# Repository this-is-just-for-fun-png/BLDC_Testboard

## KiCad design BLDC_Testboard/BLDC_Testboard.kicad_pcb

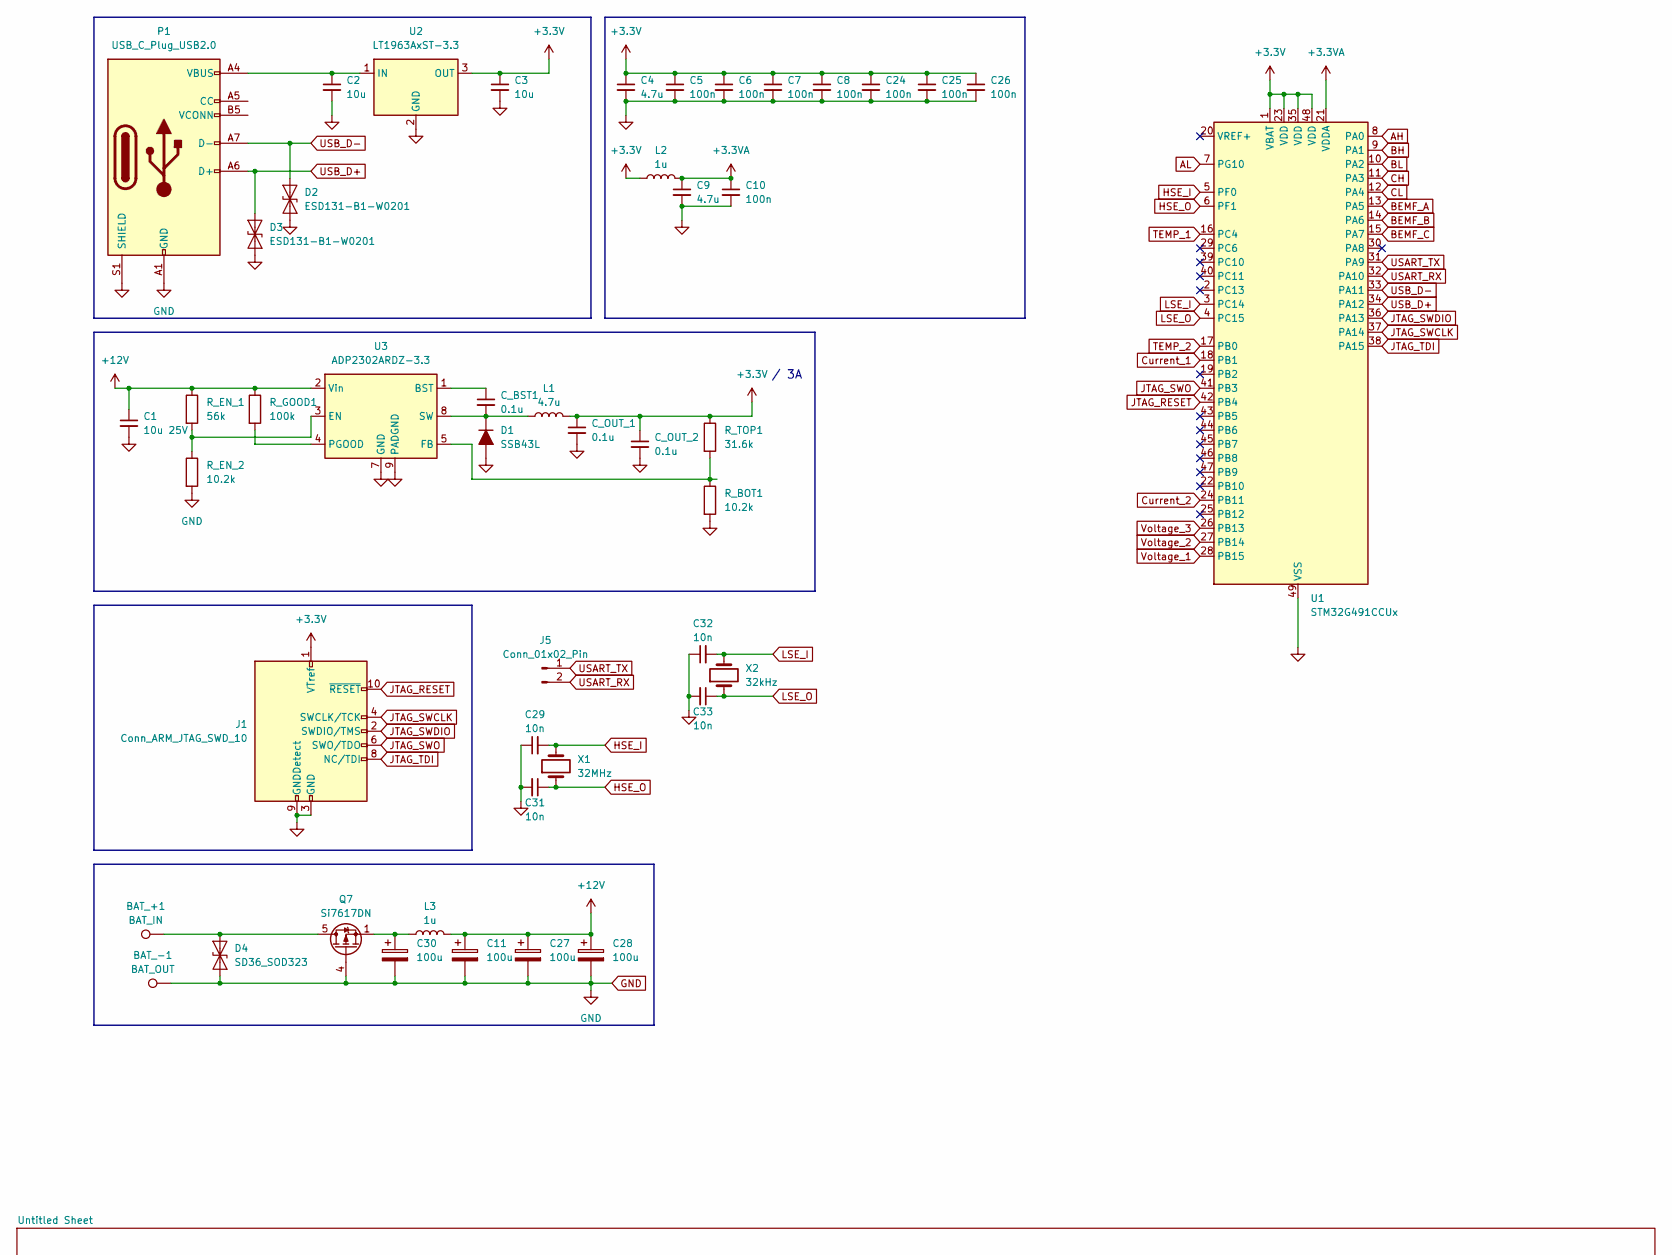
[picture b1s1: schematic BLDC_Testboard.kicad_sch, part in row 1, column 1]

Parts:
BAT_+1: BAT_IN; SolderWire-2.5sqmm_1x01_D2.4mm_OD4.4mm
BAT_-1: BAT_OUT; SolderWire-2.5sqmm_1x01_D2.4mm_OD4.4mm
C1: 10u 25V; C_0201_0603Metric
C2, C3: 10u; C_0201_0603Metric
C4, C9: 4.7u; C_0201_0603Metric
C5, C6, C7, C8, C10, C24, C25, C26: 100n; C_0201_0603Metric
C11, C27, C28, C30: 100u; CP_Elec_3x5.3
C29, C31, C32, C33: 10n; C_0201_0603Metric
C_BST1: 0.1u; C_0201_0603Metric
C_OUT_1, C_OUT_2: 0.1u; C_0201_0603Metric
D1: SSB43L; D_SMB
D2, D3: ESD131-B1-W0201; Infineon_SG-WLL-2-3_0.58x0.28_P0.36mm
D4: SD36_SOD323; D_SOD-323
J1: Conn_ARM_JTAG_SWD_10; PinHeader_2x05_P1.27mm_Vertical_SMD
J5: Conn_01x02_Pin; PinHeader_1x02_P1.00mm_Vertical
L1: 4.7u; L_0201_0603Metric
L2, L3: 1u; L_0201_0603Metric
P1: USB_C_Plug_USB2.0; USB_C_Receptacle_Amphenol_12401610E4-2A
Q7: Si7617DN; Vishay_PowerPAK_1212-8_Single
R_BOT1: 10.2k; R_0201_0603Metric_Pad0.64x0.40mm_HandSolder
R_EN_1: 56k; R_0201_0603Metric_Pad0.64x0.40mm_HandSolder
R_EN_2: 10.2k; R_0201_0603Metric_Pad0.64x0.40mm_HandSolder
R_GOOD1: 100k; R_0201_0603Metric_Pad0.64x0.40mm_HandSolder
R_TOP1: 31.6k; R_0603_1608Metric_Pad0.98x0.95mm_HandSolder
U1: STM32G491CCUx; QFN-48-1EP_7x7mm_P0.5mm_EP5.6x5.6mm
U2: LT1963AxST-3.3; SOT-223-3_TabPin2
U3: ADP2302ARDZ-3.3; SOIC-8-1EP_3.9x4.9mm_P1.27mm_EP2.29x3mm
X1: 32MHz; Crystal_SMD_2012-2Pin_2.0x1.2mm_HandSoldering
X2: 32kHz; Crystal_SMD_2012-2Pin_2.0x1.2mm_HandSoldering

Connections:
+3.3V: C3.1, C4.1, C5.1, C6.1, C7.1, C8.1, C24.1, C25.1, C26.1, C_OUT_1.1, C_OUT_2.1, J1.1 (VTref), L1.2, L2.1, R_TOP1.1, U1.1 (VBAT), U1.23 (VDD), U1.35 (VDD), U1.48 (VDD), U2.3 (OUT); also elsewhere on the board
+3.3VA: C9.1, C10.1, L2.2, U1.21 (VDDA)
+12V: C1.1, C11.1, C27.1, C28.1, L3.2, R_EN_1.1, R_GOOD1.1, U3.2 (Vin); also elsewhere on the board
AH: U1.8 (PA0); also elsewhere on the board
AL: U1.7 (PG10); also elsewhere on the board
BEMF_A: U1.13 (PA5); also elsewhere on the board
BEMF_B: U1.14 (PA6); also elsewhere on the board
BEMF_C: U1.15 (PA7); also elsewhere on the board
BH: U1.9 (PA1); also elsewhere on the board
BL: U1.10 (PA2); also elsewhere on the board
CH: U1.11 (PA3); also elsewhere on the board
CL: U1.12 (PA4); also elsewhere on the board
Current_1: U1.18 (PB1)
Current_2: U1.24 (PB11)
Current_SP1-: BAT_-1.1, C1.2, C2.2, C3.2, C4.2, C5.2, C6.2, C7.2, C8.2, C9.2, C10.2, C11.2, C24.2, C25.2, C26.2, C27.2, C28.2, C29.1, C30.2, C31.2, C32.1, C33.2, C_OUT_1.2, C_OUT_2.2, D1.2 (A), D2.1 (A1), D3.1 (A1), D4.1 (A1), J1.3 (GND), J1.5 (GND), J1.9 (GNDDetect), P1.A1 (GND), P1.A12 (GND), P1.B1 (GND), P1.B12 (GND), P1.S1 (SHIELD), Q7.4 (G), R_BOT1.2, R_EN_2.2, U1.49 (VSS), U2.2 (GND), U3.7 (GND), U3.9 (PADGND); also elsewhere on the board
HSE_I: C29.2, U1.5 (PF0), X1.2
HSE_O: C31.1, U1.6 (PF1), X1.1
JTAG_RESET: J1.10 (~RESET), U1.42 (PB4)
JTAG_SWCLK: J1.4 (SWCLK/TCK), U1.37 (PA14)
JTAG_SWDIO: J1.2 (SWDIO/TMS), U1.36 (PA13)
JTAG_SWO: J1.6 (SWO/TDO), U1.41 (PB3)
JTAG_TDI: J1.8 (NC/TDI), U1.38 (PA15)
LSE_I: C32.2, U1.3 (PC14), X2.2
LSE_O: C33.1, U1.4 (PC15), X2.1
unnamed: C30.1, L3.1, Q7.1 (S), Q7.2 (S), Q7.3 (S)
unnamed: C_BST1.2, D1.1 (K), L1.1, U3.8 (SW)
unnamed: BAT_+1.1, D4.2 (A2), Q7.5 (D)
unnamed: C2.1, P1.A4 (VBUS), P1.A9 (VBUS), P1.B4 (VBUS), P1.B9 (VBUS), U2.1 (IN)
unnamed: C_BST1.1, U3.1 (BST)
unnamed: R_EN_1.2, R_EN_2.1, U3.3 (EN)
unnamed: R_BOT1.1, R_TOP1.2, U3.5 (FB)
unnamed: R_GOOD1.2, U3.4 (PGOOD)
TEMP_1: U1.16 (PC4)
TEMP_2: U1.17 (PB0)
USART_RX: J5.2, U1.32 (PA10)
USART_TX: J5.1, U1.31 (PA9)
USB_D+: D3.2 (A2), P1.A6 (D+), U1.34 (PA12)
USB_D-: D2.2 (A2), P1.A7 (D-), U1.33 (PA11)
Voltage_1: U1.28 (PB15)
Voltage_2: U1.27 (PB14)
Voltage_3: U1.26 (PB13)

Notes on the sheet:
/ 3A

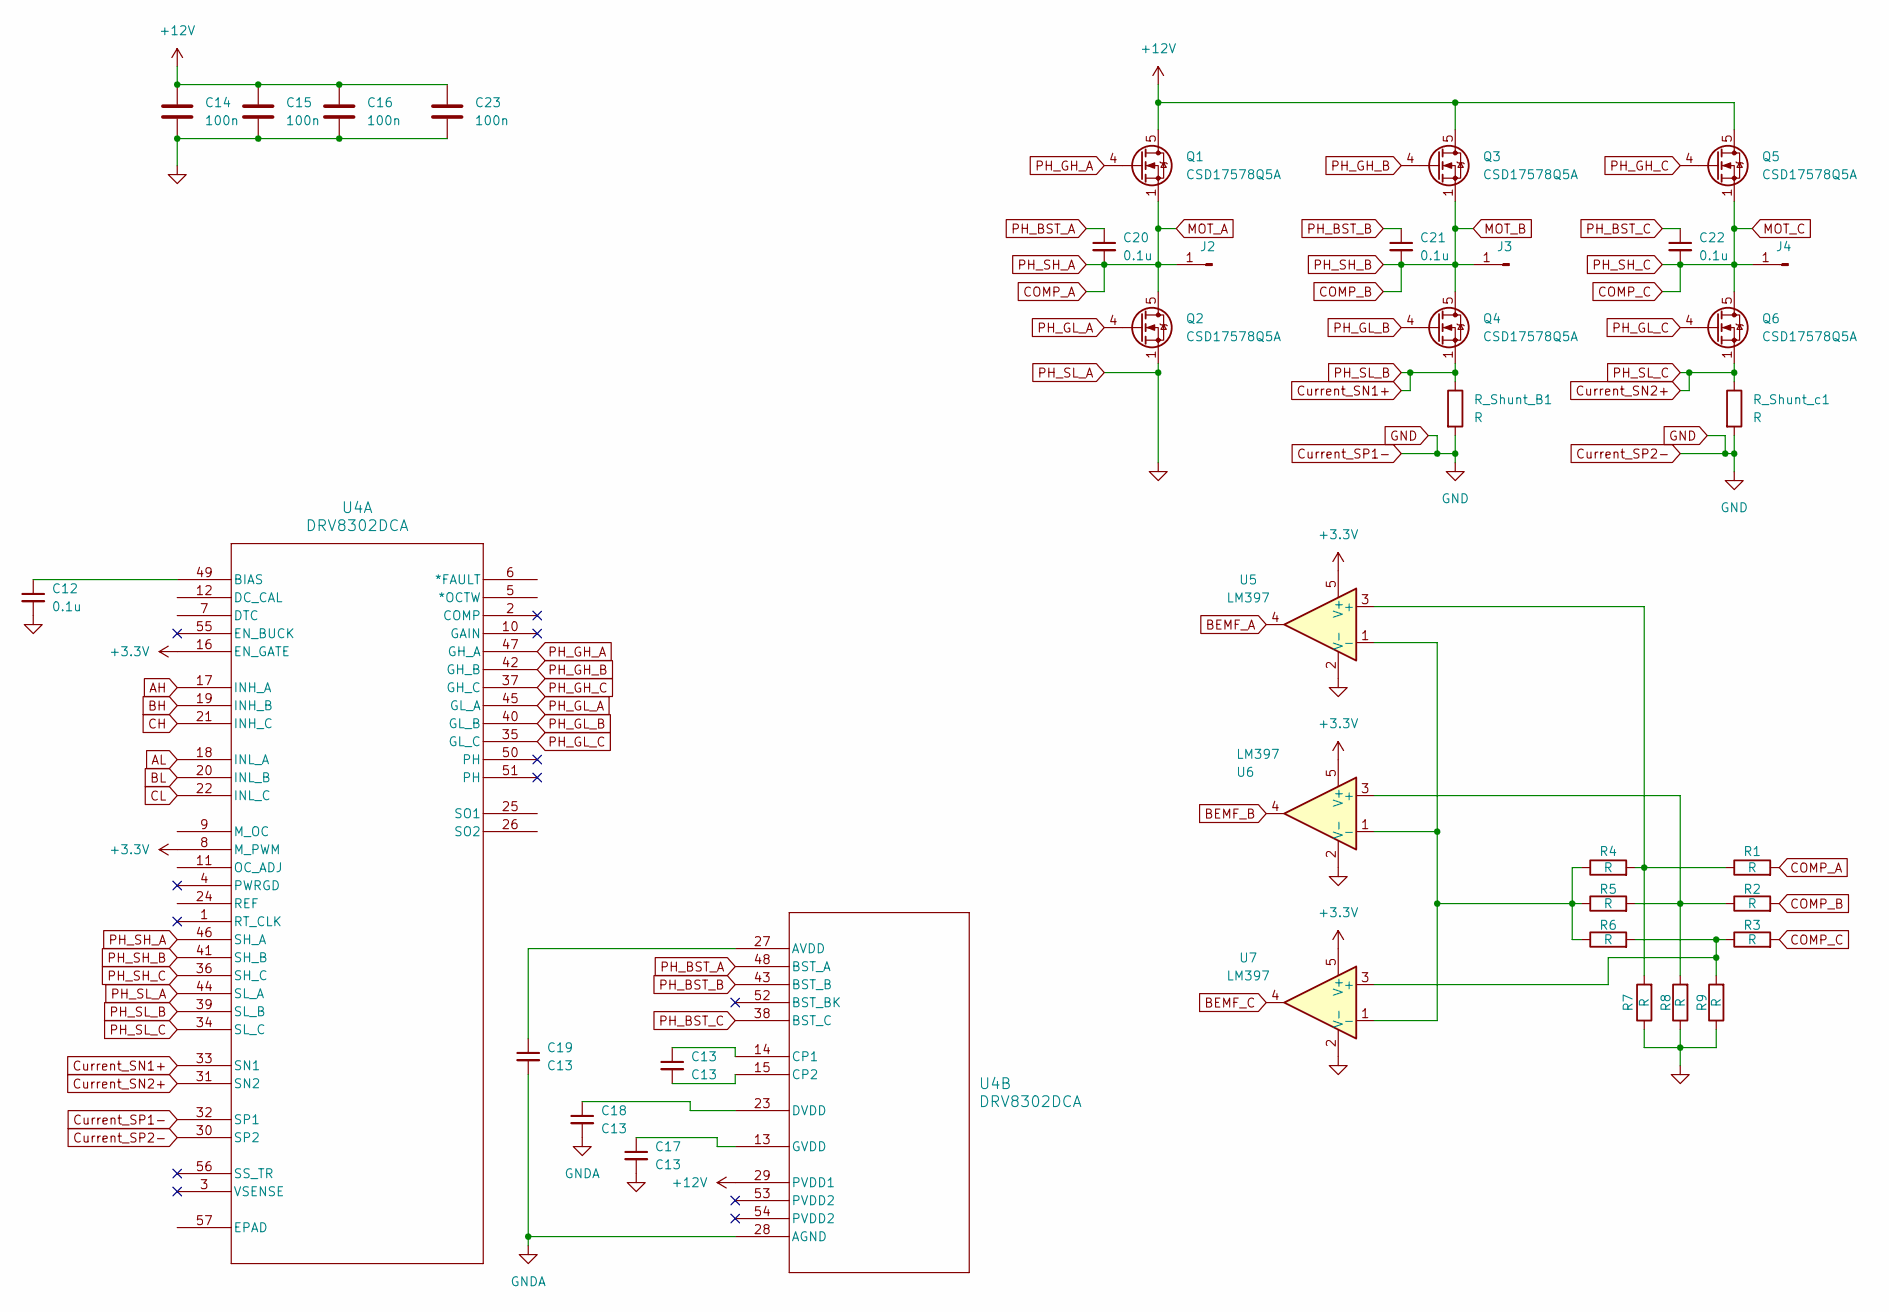
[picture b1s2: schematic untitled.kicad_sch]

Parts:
C12, C20, C21, C22: 0.1u; C_0201_0603Metric
C13, C17, C18, C19: C13; C_0201_0603Metric
C14, C15, C16, C23: 100n; C_0201_0603Metric
J2, J3, J4: Conn_01x01_Pin; SolderWire-1.5sqmm_1x01_D1.7mm_OD3.9mm
Q1, Q2, Q3, Q4, Q5, Q6: CSD17578Q5A; TDSON-8-1
R1, R2, R3, R4, R5, R6, R7, R8, R9: R; R_0201_0603Metric_Pad0.64x0.40mm_HandSolder
R_Shunt_B1: R; R_0603_1608Metric_Pad0.98x0.95mm_HandSolder
R_Shunt_c1: R; R_0603_1608Metric_Pad0.98x0.95mm_HandSolder
U4: DRV8302DCA; DCA56_6P35X3P61
U5, U6, U7: LM397; SOT-23-5

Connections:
+3.3V: U4.8 (M_PWM), U4.16 (EN_GATE), U5.5 (V+), U6.5 (V+), U7.5 (V+); also elsewhere on the board
+12V: C14.1, C15.1, C16.1, C23.1, Q1.5 (D), Q3.5 (D), Q5.5 (D), U4.29 (PVDD1); also elsewhere on the board
AH: U4.17 (INH_A); also elsewhere on the board
AL: U4.18 (INL_A); also elsewhere on the board
BEMF_A: U5.4; also elsewhere on the board
BEMF_B: U6.4; also elsewhere on the board
BEMF_C: U7.4; also elsewhere on the board
BH: U4.19 (INH_B); also elsewhere on the board
BL: U4.20 (INL_B); also elsewhere on the board
CH: U4.21 (INH_C); also elsewhere on the board
CL: U4.22 (INL_C); also elsewhere on the board
Current_SN1+: Q4.1 (S), Q4.2 (S), Q4.3 (S), R_Shunt_B1.1, U4.33 (SN1), U4.39 (SL_B)
Current_SN2+: Q6.1 (S), Q6.2 (S), Q6.3 (S), R_Shunt_c1.1, U4.31 (SN2), U4.34 (SL_C)
Current_SP1-: C12.2, C14.2, C15.2, C16.2, C17.2, C23.2, Q2.1 (S), Q2.2 (S), Q2.3 (S), R7.1, R8.1, R9.1, R_Shunt_B1.2, R_Shunt_c1.2, U4.30 (SP2), U4.32 (SP1), U4.44 (SL_A), U5.2 (V-), U6.2 (V-), U7.2 (V-); also elsewhere on the board
GNDA: C18.2, C19.2, U4.28 (AGND)
unnamed: C12.1, U4.49 (BIAS)
unnamed: C19.1, U4.27 (AVDD)
unnamed: C13.1, U4.14 (CP1)
unnamed: C13.2, U4.15 (CP2)
unnamed: C18.1, U4.23 (DVDD)
unnamed: C17.1, U4.13 (GVDD)
unnamed: R1.1, R4.2, R7.2, U5.3 (+)
unnamed: R4.1, R5.1, R6.1, U5.1 (-), U6.1 (-), U7.1 (-)
unnamed: R2.1, R5.2, R8.2, U6.3 (+)
unnamed: R3.1, R6.2, R9.2, U7.3 (+)
PH_BST_A: C20.1, U4.48 (BST_A)
PH_BST_B: C21.1, U4.43 (BST_B)
PH_BST_C: C22.1, U4.38 (BST_C)
PH_GH_A: Q1.4 (G), U4.47 (GH_A)
PH_GH_B: Q3.4 (G), U4.42 (GH_B)
PH_GH_C: Q5.4 (G), U4.37 (GH_C)
PH_GL_A: Q2.4 (G), U4.45 (GL_A)
PH_GL_B: Q4.4 (G), U4.40 (GL_B)
PH_GL_C: Q6.4 (G), U4.35 (GL_C)

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
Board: 4 copper layers, 83 parts (0 on the bottom side), 59 nets, no tracks yet.
